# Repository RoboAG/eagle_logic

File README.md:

# eagle_logic
Simple logic circuits

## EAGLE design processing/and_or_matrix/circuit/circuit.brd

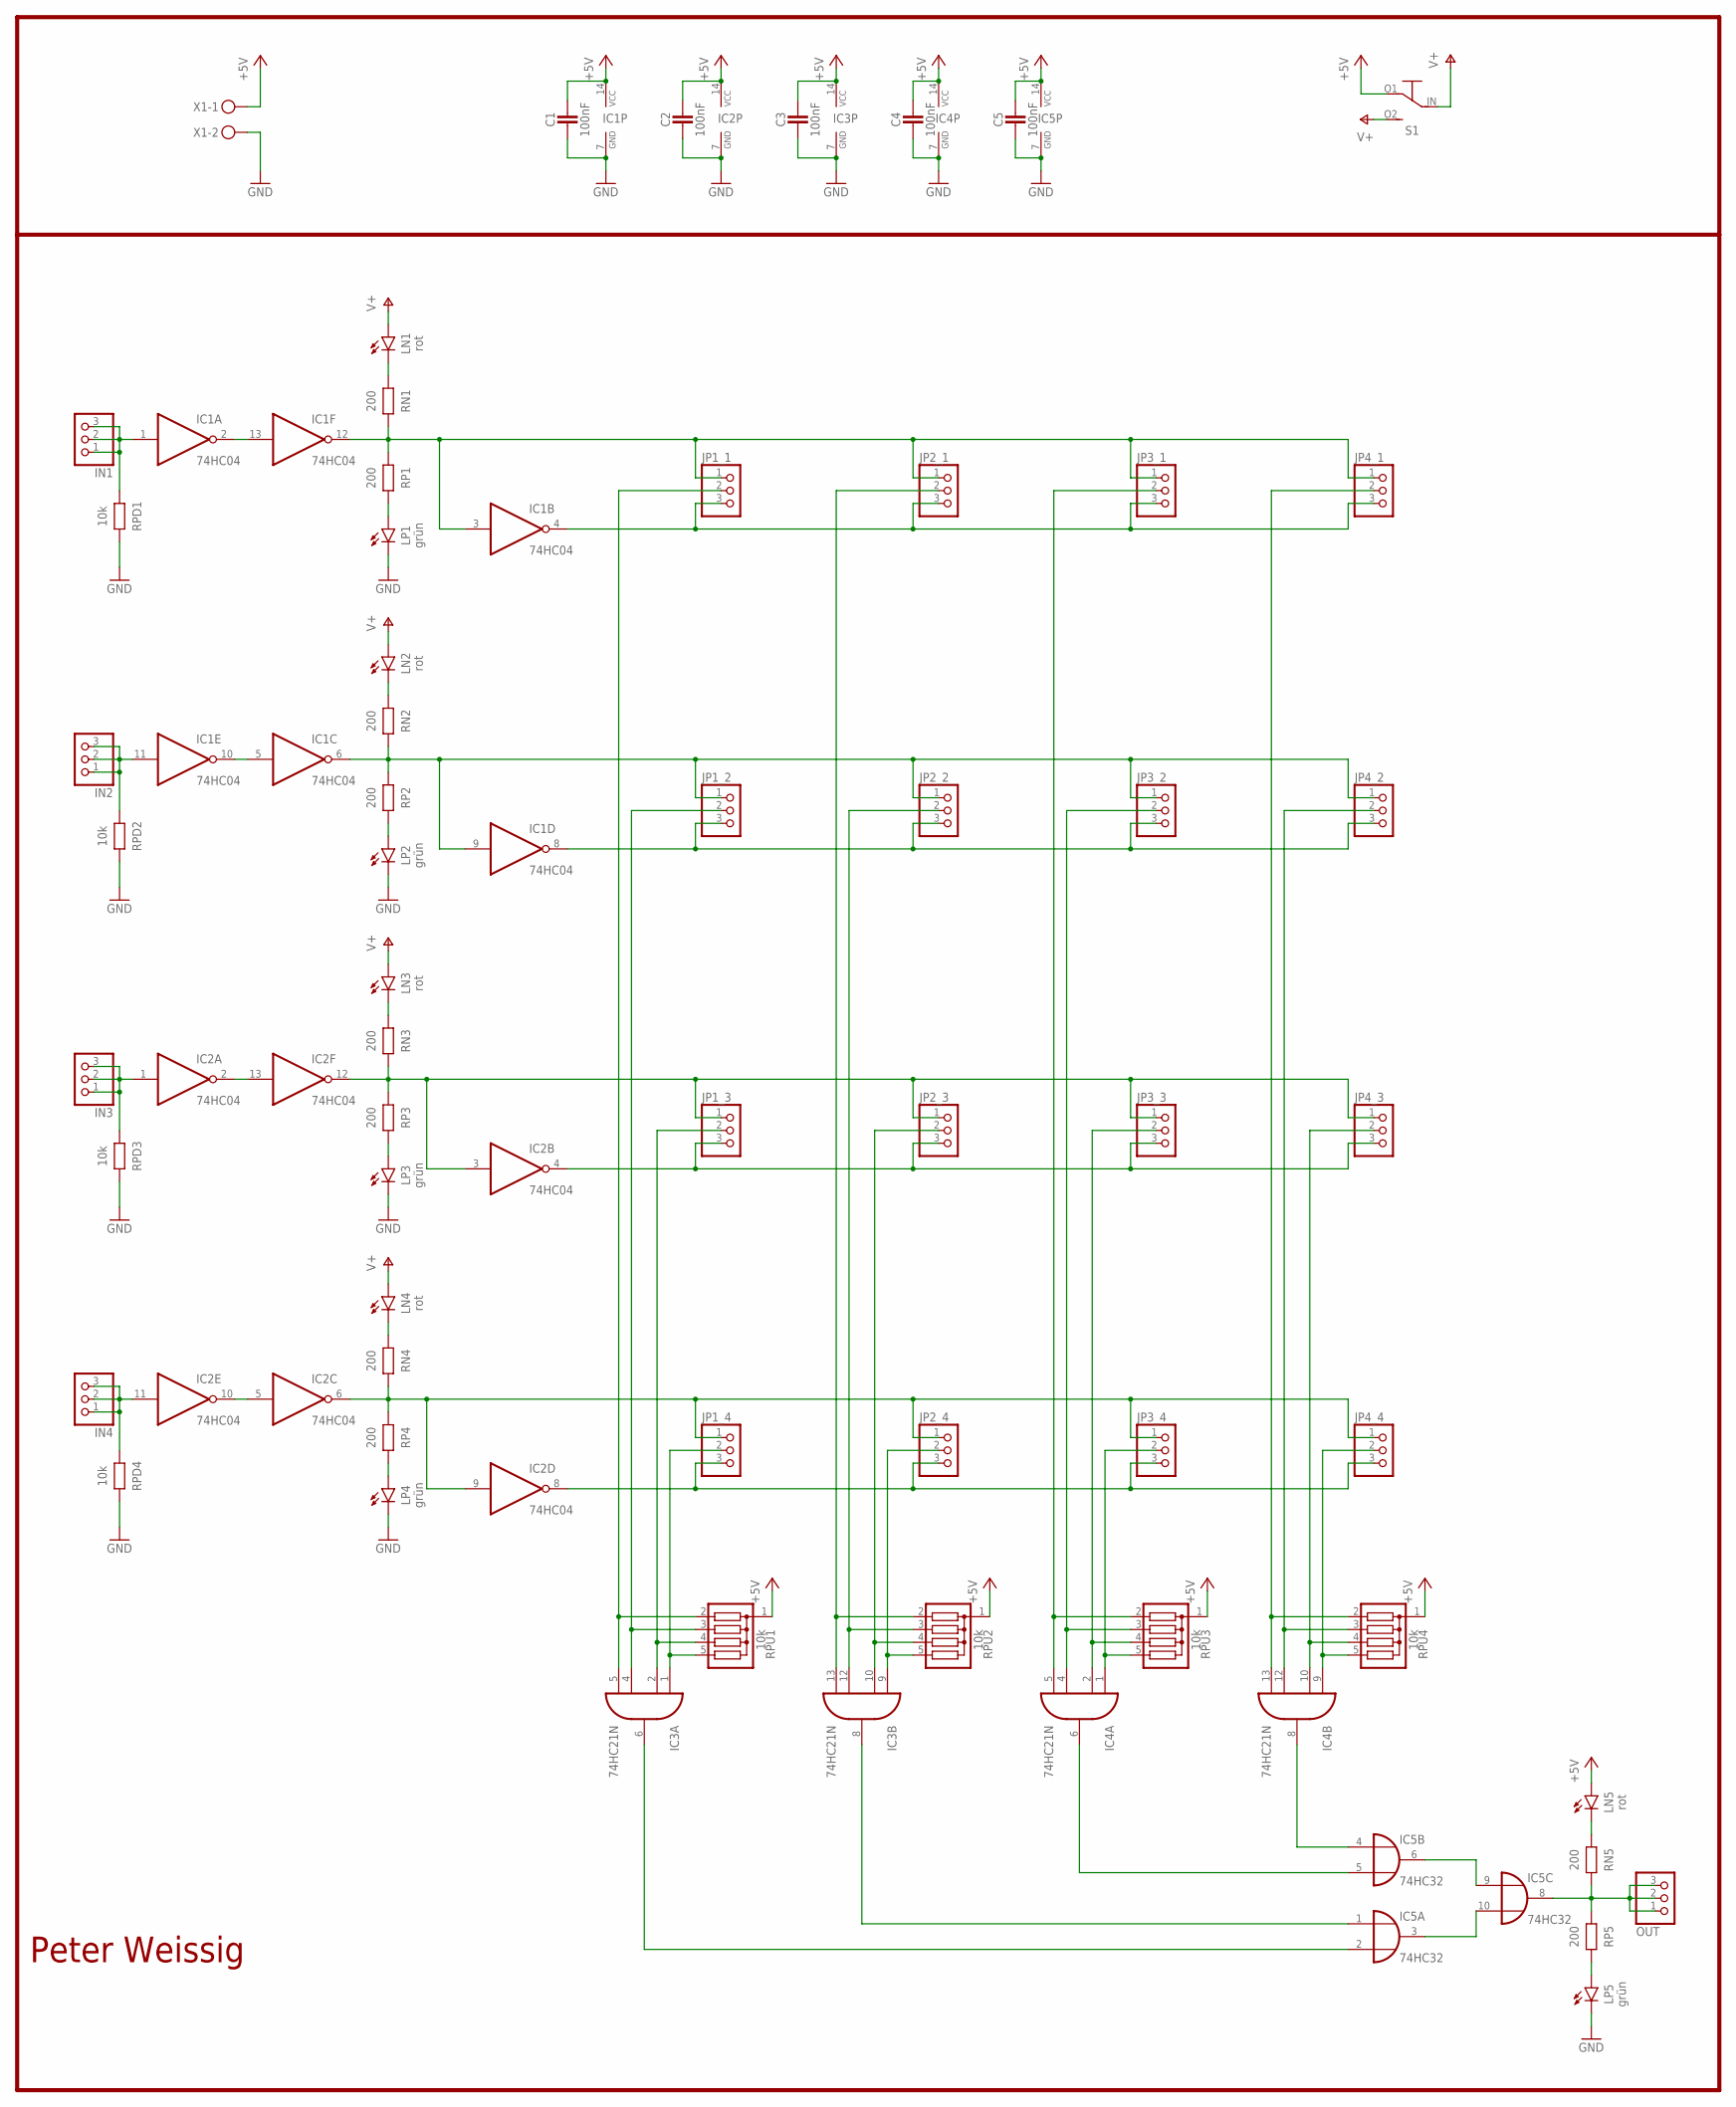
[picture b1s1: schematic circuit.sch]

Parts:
C1, C2, C5: 100nF; C_THT_2
C3, C4: 100nF; C_THT_3
IC1, IC2: 74HC04; DIL14
IC3, IC4: 74HC21N; DIL14
IC5: 74HC32; DIL14
IN1, IN2, IN3, IN4: PINHD-1X3; 1X03
JP1_1, JP1_2, JP1_3, JP1_4, JP2_1, JP2_2, JP2_3, JP2_4, JP3_1, JP3_2, JP3_3, JP3_4, JP4_1, JP4_2, JP4_3, JP4_4: PINHD-1X3; 1X03
LN1, LN2, LN3, LN4, LN5: rot; LED_3MM
LP1, LP2, LP3, LP4, LP5: grün; LED_3MM
OUT: PINHD-1X3; 1X03
RN1, RN2, RN3, RN4, RN5: 200; R_THT_4
RP1, RP2, RP3, RP4, RP5: 200; R_THT_4
RPD1, RPD2, RPD3, RPD4: 10k; R_THT_4
RPU1, RPU2, RPU3, RPU4: 10k; SIL5
S1: SCHALTER_UM-KIPP; SCHALTER_KIPP_UM
X1: STECKER_SPG_2

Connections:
+5V: C1.1, C2.1, C3.1, C4.1, C5.1, IC1.14 (VCC), IC2.14 (VCC), IC3.14 (VCC), IC4.14 (VCC), IC5.14 (VCC), LN5.A, RPU1.1, RPU2.1, RPU3.1, RPU4.1, S1.O1, X1.1
GND: C1.2, C2.2, C3.2, C4.2, C5.2, IC1.7 (GND), IC2.7 (GND), IC3.7 (GND), IC4.7 (GND), IC5.7 (GND), LP1.K (C), LP2.K (C), LP3.K (C), LP4.K (C), LP5.K (C), RPD1.1, RPD2.1, RPD3.1, RPD4.1, X1.2
unnamed: IC3.5 (I3), JP1_1.2, RPU1.2
unnamed: LN1.K (C), RN1.2
unnamed: IC3.13 (I3), JP2_1.2, RPU2.2
unnamed: LP2.A, RP2.1
unnamed: IC3.12 (I2), JP2_2.2, RPU2.3
unnamed: LN2.K (C), RN2.2
unnamed: LP1.A, RP1.1
unnamed: LP3.A, RP3.1
unnamed: LN3.K (C), RN3.2
unnamed: IC3.10 (I1), JP2_3.2, RPU2.4
unnamed: LP4.A, RP4.1
unnamed: LN4.K (C), RN4.2
unnamed: IC1.1 (I), IN1.1, IN1.2, IN1.3, RPD1.2
unnamed: IC1.11 (I), IN2.1, IN2.2, IN2.3, RPD2.2
unnamed: IC3.9 (I0), JP2_4.2, RPU2.5
unnamed: IC4.5 (I3), JP3_1.2, RPU3.2
unnamed: IC4.4 (I2), JP3_2.2, RPU3.3
unnamed: IC2.11 (I), IN4.1, IN4.2, IN4.3, RPD4.2
unnamed: IC4.2 (I1), JP3_3.2, RPU3.4
unnamed: IC4.1 (I0), JP3_4.2, RPU3.5
unnamed: IC1.2 (O), IC1.13 (I)
unnamed: IC1.5 (I), IC1.10 (O)
unnamed: IC2.5 (I), IC2.10 (O)
unnamed: IC2.2 (O), IC2.13 (I)
unnamed: IC3.4 (I2), JP1_2.2, RPU1.3
unnamed: IC3.2 (I1), JP1_3.2, RPU1.4
unnamed: IC3.1 (I0), JP1_4.2, RPU1.5
unnamed: IC4.13 (I3), JP4_1.2, RPU4.2
unnamed: IC4.12 (I2), JP4_2.2, RPU4.3
unnamed: IC4.10 (I1), JP4_3.2, RPU4.4
unnamed: IC4.9 (I0), JP4_4.2, RPU4.5
unnamed: IC4.8 (O), IC5.4 (I0)
unnamed: IC4.6 (O), IC5.5 (I1)
unnamed: IC3.8 (O), IC5.1 (I0)
unnamed: IC3.6 (O), IC5.2 (I1)
unnamed: IC5.6 (O), IC5.9 (I0)
unnamed: IC5.3 (O), IC5.10 (I1)
unnamed: LP5.A, RP5.1
unnamed: LN5.K (C), RN5.2
unnamed: IC2.1 (I), IN3.1, IN3.2, IN3.3, RPD3.2
N_1N: IC1.4 (O), JP1_1.3, JP2_1.3, JP3_1.3, JP4_1.3
N_1P: IC1.3 (I), IC1.12 (O), JP1_1.1, JP2_1.1, JP3_1.1, JP4_1.1, RN1.1, RP1.2
N_2N: IC1.8 (O), JP1_2.3, JP2_2.3, JP3_2.3, JP4_2.3
N_2P: IC1.6 (O), IC1.9 (I), JP1_2.1, JP2_2.1, JP3_2.1, JP4_2.1, RN2.1, RP2.2
N_3N: IC2.4 (O), JP1_3.3, JP2_3.3, JP3_3.3, JP4_3.3
N_3P: IC2.3 (I), IC2.12 (O), JP1_3.1, JP2_3.1, JP3_3.1, JP4_3.1, RN3.1, RP3.2
N_4N: IC2.8 (O), JP1_4.3, JP2_4.3, JP3_4.3, JP4_4.3
N_4P: IC2.6 (O), IC2.9 (I), JP1_4.1, JP2_4.1, JP3_4.1, JP4_4.1, RN4.1, RP4.2
N_4P1: IC5.8 (O), OUT.1, OUT.2, OUT.3, RN5.1, RP5.2
V+: LN1.A, LN2.A, LN3.A, LN4.A, S1.IN, S1.O2

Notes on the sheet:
Peter Weissig

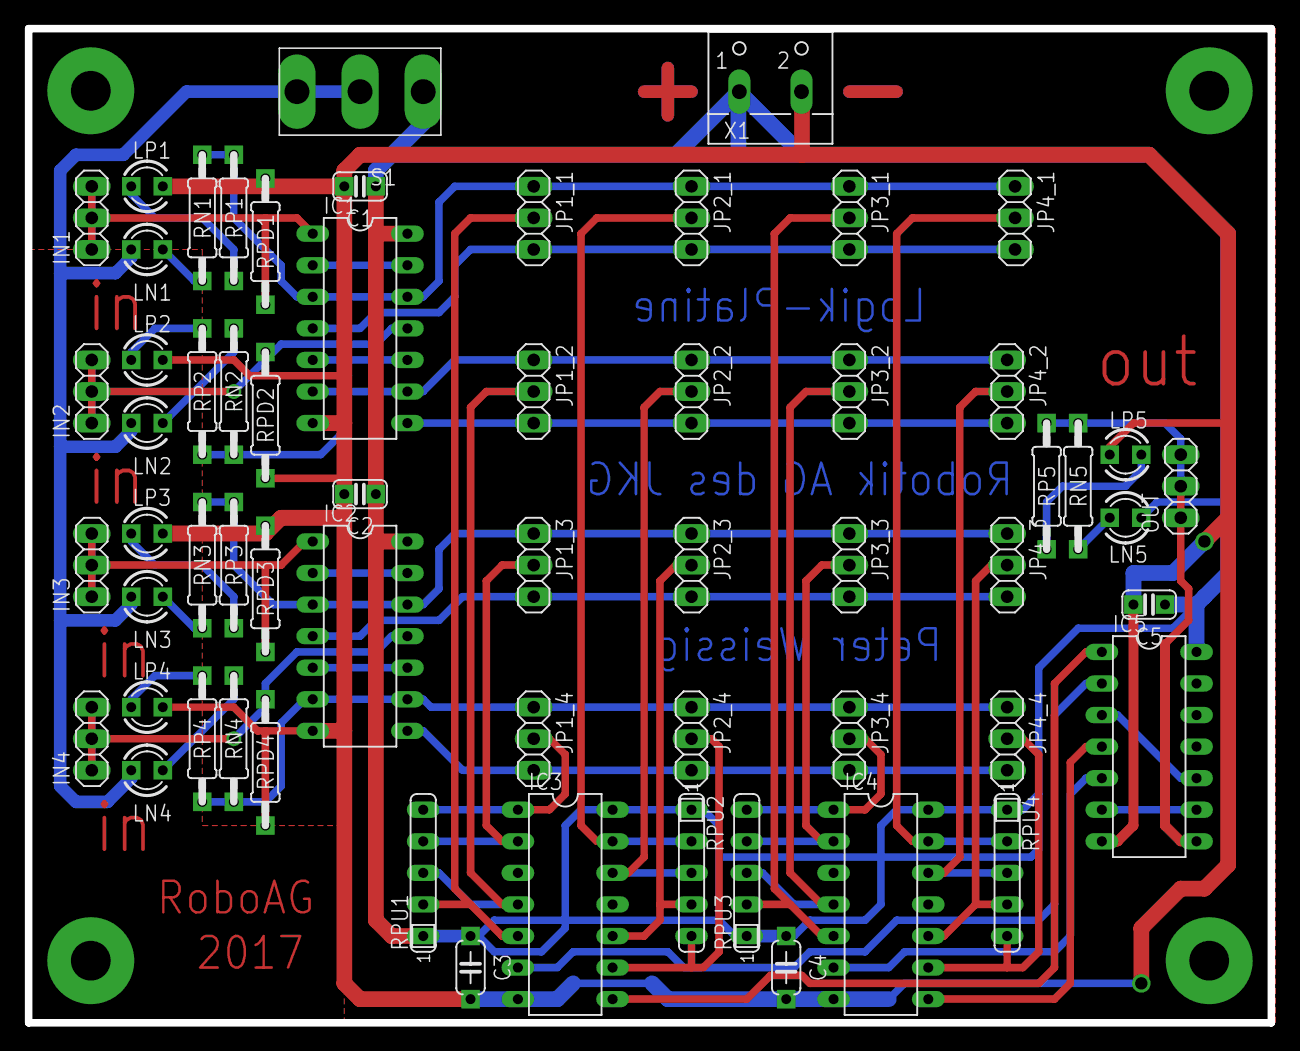
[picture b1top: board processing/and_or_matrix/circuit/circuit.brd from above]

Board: 2 copper layers, 100.0 x 80.0 mm, 61 parts (0 on the bottom side), 52 nets.

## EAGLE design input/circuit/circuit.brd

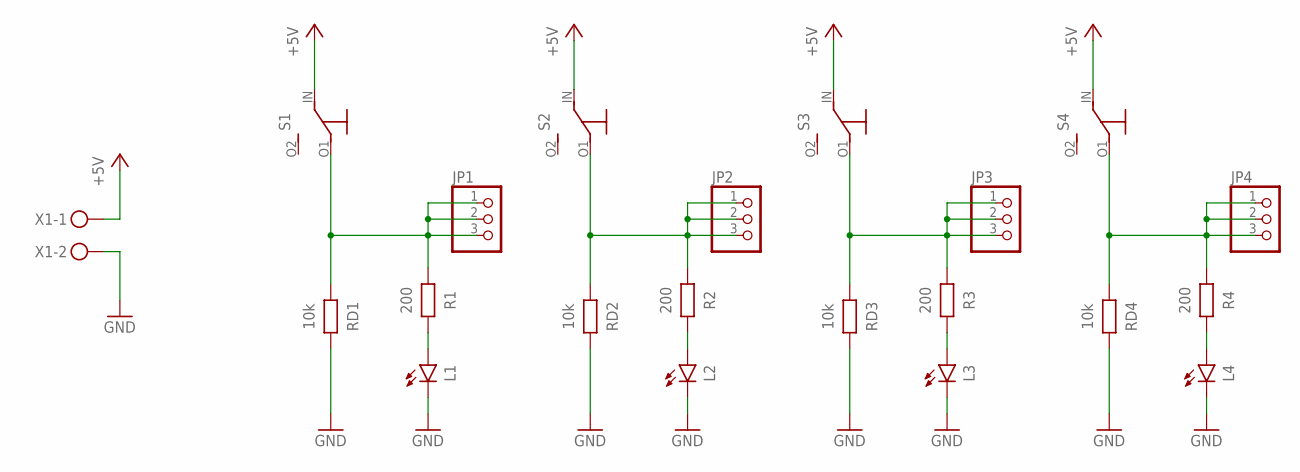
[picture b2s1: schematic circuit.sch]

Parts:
JP1, JP2, JP3, JP4: PINHD-1X3; 1X03
L1, L2, L3, L4: LED-3MM; LED_3MM
R1, R2, R3, R4: 200; R_THT_4
RD1, RD2, RD3, RD4: 10k; R_THT_4
S1, S2, S3, S4: SCHALTER_UM-KIPP; SCHALTER_KIPP_UM
X1: STECKER_SPG_2

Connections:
+5V: S1.IN, S2.IN, S3.IN, S4.IN, X1.1
GND: L1.K (C), L2.K (C), L3.K (C), L4.K (C), RD1.1, RD2.1, RD3.1, RD4.1, X1.2
unnamed: JP2.1, JP2.2, JP2.3, R2.2, RD2.2, S2.O1
unnamed: L2.A, R2.1
unnamed: JP3.1, JP3.2, JP3.3, R3.2, RD3.2, S3.O1
unnamed: L3.A, R3.1
unnamed: JP1.1, JP1.2, JP1.3, R1.2, RD1.2, S1.O1
unnamed: JP4.1, JP4.2, JP4.3, R4.2, RD4.2, S4.O1
unnamed: L4.A, R4.1
unnamed: L1.A, R1.1

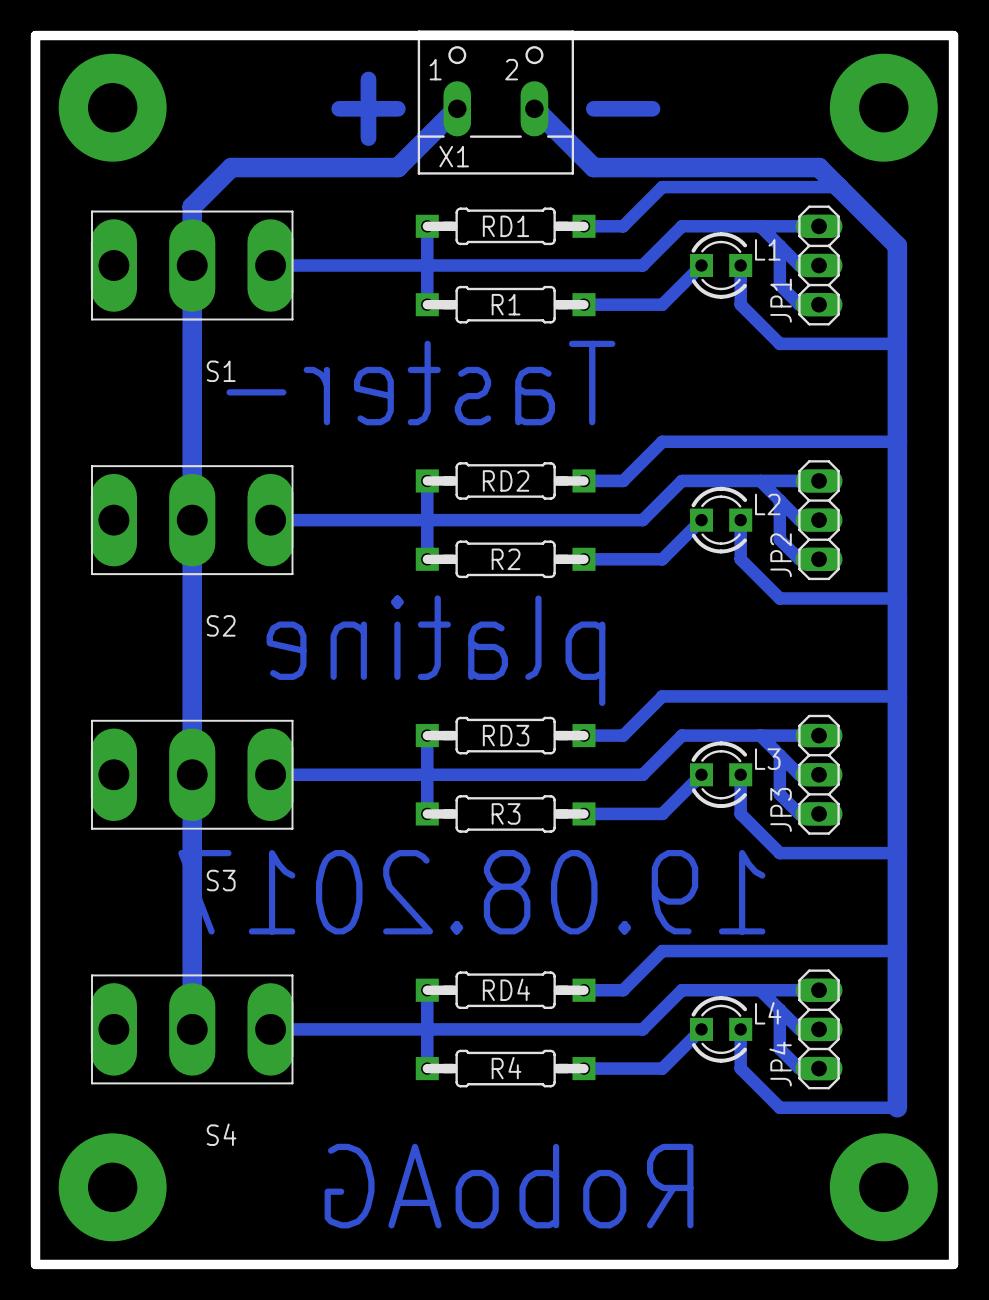
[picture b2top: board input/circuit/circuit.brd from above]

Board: 2 copper layers, 59.5 x 79.7 mm, 21 parts (0 on the bottom side), 10 nets.

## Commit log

2017-11-27 added circuit for processing (4x4 and-or-matrix)
2018-01-04 updated processing unit + minor changes (renamed some resistors, added some values, moved names of leds) + added parts
